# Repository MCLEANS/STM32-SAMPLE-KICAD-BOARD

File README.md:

# STM32-SAMPLE-KICAD-BOARD
A sample STM32 board using KiCAD.

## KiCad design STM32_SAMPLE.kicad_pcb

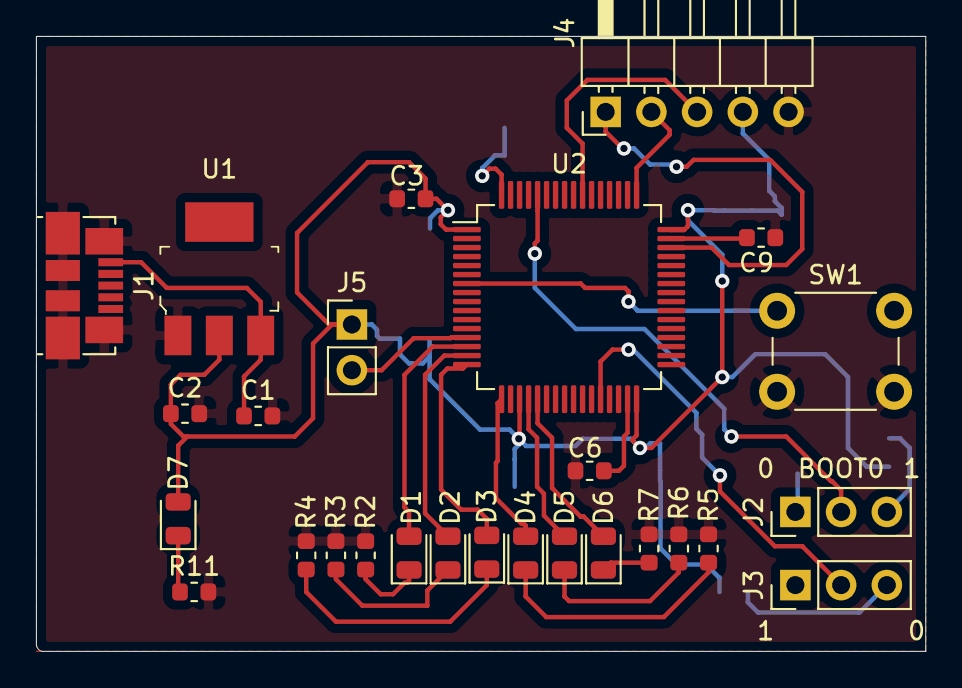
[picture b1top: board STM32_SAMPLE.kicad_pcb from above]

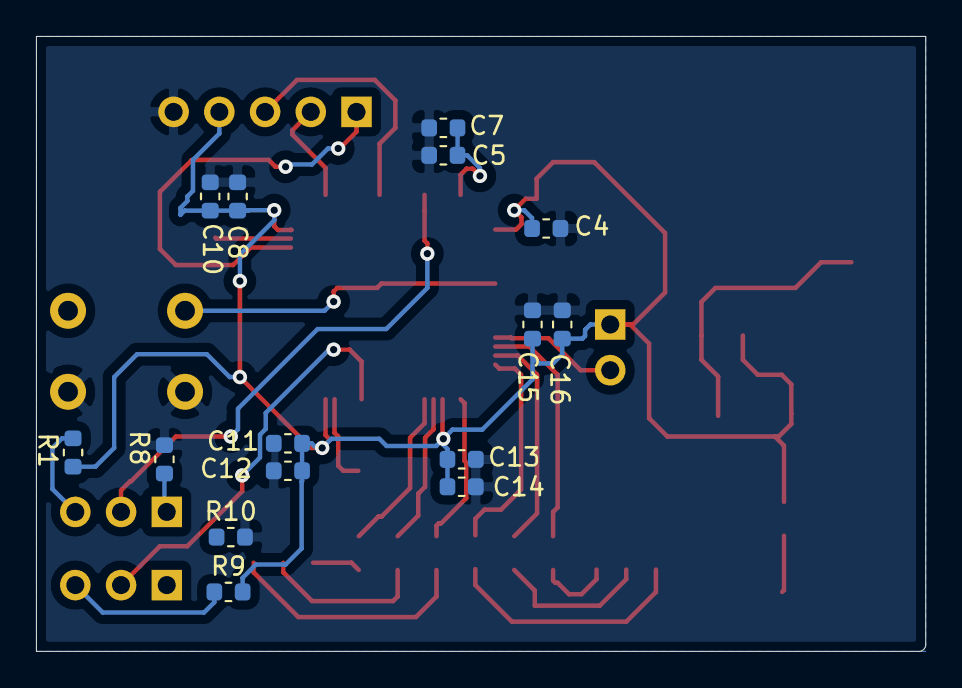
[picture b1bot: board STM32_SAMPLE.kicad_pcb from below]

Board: 2 copper layers, 49.4 x 34.2 mm, 42 parts (15 on the bottom side), 29 nets.

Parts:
C1, C2, C3: 10uF; C_0603_1608Metric
C4, C5, C7, C8, C10, C11, C12, C13, C14, C15: 100nF; C_0603_1608Metric
C6, C9: 2.2uF; C_0603_1608Metric
C16: 1uF; C_0603_1608Metric
D1, D2, D3, D4, D5, D6, D7: LED; LED_0805_2012Metric
J1: USB_B_Micro; USB_Micro-B_Molex_47346-0001
J2, J3: Conn_01x03_Male; PinHeader_1x03_P2.54mm_Vertical
J4: Conn_01x05_Male; PinHeader_1x05_P2.54mm_Horizontal
J5: Conn_01x02_Male; PinHeader_1x02_P2.54mm_Vertical
R1, R8, R9, R10: 10K; R_0603_1608Metric
R2, R3, R4, R5, R6, R7, R11: 220ohms; R_0603_1608Metric
SW1: SW_Push; SW_PUSH_6mm_H5mm
U1: LM1117-3.3; SOT-223
U2: STM32F405RGTx; LQFP-64_10x10mm_P0.5mm

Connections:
+3V3: C2.1, C3.1, C4.1, C5.1, C7.1, C8.1, C10.1, C11.1, C12.1, C13.1, C14.1, C15.1, C16.1, D7.2, J4.4, J5.1, R1.2, R9.2, U1.2, U2.1, U2.19, U2.32, U2.48, U2.64
+5V: C1.1, J1.1, U1.3
BOOT0: J2.2, U2.60
BOOT1: J3.2, U2.28
GND: C1.2, C2.2, C3.2, C4.2, C5.2, C6.2, C7.2, C8.2, C9.2, C10.2, C11.2, C12.2, C13.2, C14.2, C15.2, C16.2, J1.4, J1.5, J1.6, J4.5, R2.1, R3.1, R4.1, R5.1, R6.1, R7.1, R8.1, R10.2, R11.2, SW1.2, U1.1, U2.12, U2.18, U2.63
NRST: SW1.1, U2.7
unnamed: C6.1, U2.31
unnamed: C9.1, U2.47
unnamed: D1.1, R2.2
unnamed: D1.2, U2.14
unnamed: D2.1, R3.2
unnamed: D2.2, U2.15
unnamed: D3.1, R4.2
unnamed: D3.2, U2.16
unnamed: D4.1, R5.2
unnamed: D4.2, U2.17
unnamed: D5.1, R6.2
unnamed: D5.2, U2.20
unnamed: D6.1, R7.2
unnamed: D6.2, U2.21
unnamed: D7.1, R11.1
unnamed: J2.1, R8.2
unnamed: J2.3, R1.1
unnamed: J3.1, R10.1
unnamed: J3.3, R9.1
SWDCLK: J4.2, U2.49
SWDIO: J4.1, U2.46
SWO: J4.3, U2.55
VDDA: J5.2, U2.13

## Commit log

2020-04-12 Kicad project file
2020-04-12 Kicad schematic file
2020-04-12 Kicad layout file
2020-04-12 decoupled power supply
2020-04-12 STM32 board bare minimum with HSI clock
2020-04-12 generated netlist
2020-04-12 circuit layout file
2020-04-12 updated VDDA jumper
2020-04-12 grounded top and bottom planes
2020-04-12 project netlist
2020-04-12 completed routing
2020-04-13 final netlist
2020-04-13 grounded mounting holes
2020-04-13 grounding of top and bottom planes
2020-04-13 Final circuit
2020-04-13 updated LED symbol
2020-09-01 updated doc
